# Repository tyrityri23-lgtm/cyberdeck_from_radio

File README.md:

CyberDeck from Radio
A portable cyberdeck built by converting an old radio enclosure into a functional computer with a custom keyboard, custom electronics, display, battery power and a single-board computer.
> **Submission note:** Replace the image placeholders in this README with photographs/renders of the *actual completed build* before submitting this project for review.
Overview
The goal of this project is to reuse the enclosure of an old radio and turn it into a portable computer while designing the mechanical and electronic interfaces around the new hardware.
The project is divided into four main systems:
Compute system — a single-board computer runs the operating system and applications.
Input system — a custom mechanical keyboard is scanned by a dedicated XIAO ESP32-C3 controller through an MCP23017 I/O expander.
Display and power — an internal display is mounted into the original radio opening and the computer is powered from a portable power source.
Mechanical system — custom CAD parts adapt the radio enclosure to the keyboard, electronics, display and mounting hardware.
Final Build
<!-- Replace this file with a real photo/render of the assembled final device: assets/final-model.jpg -->

The cover image for the GitHub repository should use the same real final-build photograph/render, not a concept image.
System Architecture
```mermaid
flowchart LR
    K[Mechanical keyboard switches] --> M[MCP23017 I/O expander]
    M --> E[XIAO ESP32-C3]
    E --> H[BLE HID keyboard]
    H --> C[CyberDeck computer / SBC]
    C --> D[Internal display]
    P[Power bank / battery system] --> C
    P --> E
    G[BNO055 gyroscope] --> E
    S[PMW3360 optical sensor] --> E
```
The ESP32-C3 is used as a dedicated input controller rather than making the main computer scan every switch itself. This keeps the keyboard scanning logic separate from the main operating system.
Hardware
Part	Purpose	Status / note
XIAO ESP32-C3	Keyboard controller	Used for keyboard scanning and BLE HID
MCP23017	16-bit I/O expander	Provides the GPIO used by the keyboard matrix
Mechanical switches	Keyboard input	Custom keyboard
Keycaps	Physical key interface	Custom keyboard
Single-board computer	Main computer	Choose one final platform and use it consistently in the docs
Internal display	Main visual output	Mounted in the radio enclosure
Power bank / battery system	Portable power	Verify final power wiring before publication
BNO055	Motion sensor	Mentioned by the build instructions; verify final assembly
PMW3360	Optical motion sensor	Mentioned by the build instructions; verify final assembly
Custom PCB	Keyboard/electronics board	Document the actual board revision used
Important hardware consistency check
The original repository currently mentions a Radxa X4 as the main computer in the README, while the BOM also contains a LattePanda IOTA N150 and RAM/storage parts. Before the final submission, pick the computer actually installed in the finished build and update the README, instructions, CAD and BOM so they all describe the same hardware.
Keyboard Electronics
Why use an ESP32-C3?
The main computer is responsible for running the operating system and applications. The ESP32-C3 is instead dedicated to reading the physical keyboard and handling the input-side firmware.
The MCP23017 is a 16-bit I/O expander connected over I2C. It lets the controller access more matrix lines than would be convenient using only the ESP32-C3's local GPIO.
The XIAO ESP32-C3 exposes I2C on D4/GPIO6 (SDA) and D5/GPIO7 (SCL) on the current Seeed pin map. citehttps://wiki.seeedstudio.com/XIAO_ESP32C3_Getting_Started/
```text
Keyboard switches
       |
       v
+------------------+
| Keyboard matrix  |
+------------------+
       |
       v
+------------------+       I2C       +------------------+
|   MCP23017       | <--------------> | XIAO ESP32-C3    |
| 16-bit GPIO exp. |                  | firmware         |
+------------------+                  +------------------+
                                             |
                                             v
                                      BLE HID keyboard
                                             |
                                             v
                                       Main computer
```
Matrix scanning
A keyboard matrix reduces the number of connections needed for many switches by arranging them in rows and columns. The firmware drives one row at a time and reads the column states. When a switch joins the selected row to a column, the firmware records that key as pressed.
The exact row/column mapping must match the actual PCB schematic. The firmware included in this package therefore keeps the mapping in one clearly marked configuration section instead of hiding the pin assignments throughout the code.
Schematic Documentation
Add these images from KiCad before submitting:
`assets/schematic-overview.png` — complete schematic
`assets/schematic-keyboard.png` — keyboard matrix and controller section
`assets/schematic-power.png` — power section
`assets/schematic-sensors.png` — sensor section, if the sensors are installed
For each image, add 2–4 sentences describing what the section does and why the components are connected that way.
What to explain
MCP23017 section
Explain that the MCP23017 communicates with the XIAO ESP32-C3 over I2C and exposes the GPIO used by the keyboard matrix.
Keyboard matrix section
Explain the row/column arrangement and the function of the switch diodes. The diode orientation must match the actual schematic/PCB silkscreen.
Sensor section
If the BNO055 and PMW3360 are part of the final build, document their actual buses, addresses, power voltage and interrupt/data lines from the final schematic.
Power section
Document the actual battery/power-bank output, any regulators or protection circuitry, and which subsystem receives which voltage.
PCB Design
The PCB source should be kept in the repository together with its KiCad schematic and board file.
Recommended screenshots:

PCB design goals
Keep the keyboard matrix wiring organized.
Keep I2C connections short and easy to inspect.
Provide accessible mounting holes.
Label connectors and important signals on silkscreen.
Make the board easy to assemble and troubleshoot.
Firmware
Firmware lives in `firmware/`.
Important USB detail
The ESP32-C3's integrated USB interface is USB Serial/JTAG and CDC, not a reconfigurable USB HID interface. Espressif's documentation explicitly states that the ESP32-C3 supports USB CDC and JTAG, while USB HID device support is available on ESP32-S2/S3. citeturn643326search0turn643326search2
For the current XIAO ESP32-C3 hardware, the firmware in this repository uses Bluetooth Low Energy HID for the keyboard connection. The XIAO ESP32-C3 supports Bluetooth LE, and current BLE-HID libraries support ESP32-C3. citeturn656599view0turn810315view0
If the finished PCB is required to behave as a wired USB HID keyboard, the controller should instead be changed to a USB-HID-capable ESP32-S2/S3-class device and the hardware design must be updated accordingly.
Firmware responsibilities
The firmware is responsible for:
initializing I2C;
initializing the MCP23017;
scanning the keyboard matrix;
debouncing switch transitions;
translating matrix positions into keyboard actions;
advertising/pairing as a BLE HID keyboard; and
reporting input to the host.
CAD / Mechanical Design
The CAD model should show the complete physical assembly, not just an empty shell.
Recommended assembly contents:
original radio enclosure;
display and display bracket;
keyboard plate and switches;
keyboard PCB;
XIAO ESP32-C3;
main computer/SBC;
battery/power-bank location;
mounting bosses/screws;
cable routing;
ventilation openings;
external connectors and controls;
any mouse/trackball/optical-sensor hardware actually used.
Mechanical requirements before final submission
Increase enclosure wall thickness to a clearly manufacturable value appropriate for the printing method.
Add screw bosses and mounting points where parts need to be secured.
Add openings for every connector that must be accessible from outside the case.
Add ventilation around heat-producing electronics.
Add mechanical details/design features so the enclosure looks intentionally designed rather than like a plain box.
Insert simplified electronic models into the assembly so a reviewer can understand the internal layout.
STEP Files
Export the final mechanical parts and the complete assembly to STEP and place them in `cad/step/`.
Recommended exports:
```text
cad/step/
├── final_assembly.step
├── enclosure.step
├── keyboard_plate.step
├── keyboard_case.step
└── mounting_parts.step
```
Assembly
The final assembly should be documented with photos showing the progression from subassemblies to the complete device.
```text
PCB assembly
    ↓
Keyboard assembly
    ↓
Electronics mounted in case
    ↓
Display installed
    ↓
Power and signal wiring
    ↓
Final enclosure closed
    ↓
Boot/test
```
Testing
Record the results of these tests before final submission:
Test	Result	Evidence
ESP32-C3 powers on	TODO	Photo/video
MCP23017 detected on I2C	TODO	Serial log
Every keyboard key works	TODO	Key test
BLE keyboard pairs	TODO	Host screenshot
Display works	TODO	Photo
Main computer boots	TODO	Photo
Power system works safely	TODO	Test notes
Final enclosure fits	TODO	Final photo
Sensors work (if installed)	TODO	Serial/test result
Bill of Materials
The existing `bom.csv` contains the component list and purchase links. Clean it up before submission so that it only contains the actual parts used by the final build, with correct quantities and prices.
In particular, reconcile the current computer choice and verify that the sensor and PCB parts listed in the build instructions also appear in the BOM when they are actually used.
Repository Structure
```text
cyberdeck_from_radio/
├── README.md
├── instructions.md
├── bom.csv
├── firmware/
│   ├── platformio.ini
│   ├── README.md
│   └── src/
│       └── main.cpp
├── docs/
│   ├── SCHEMATIC_GUIDE.md
│   ├── CAD_AND_RENDER_GUIDE.md
│   └── FINAL_SUBMISSION_CHECKLIST.md
├── assets/
│   ├── final-model.jpg
│   ├── schematic-overview.png
│   ├── schematic-keyboard.png
│   ├── pcb-front.png
│   ├── pcb-back.png
│   └── pcb-3d.png
├── cad/
│   └── step/
└── Footprints_and__libraries/
```
Current Limitations / Next Steps
The final version should only mark a feature as complete after it has been physically tested. Hardware that is planned but not installed should remain clearly labelled as planned.
Credits
Built as an independent hardware project using KiCad for electronics design, CAD software for the mechanical design, and embedded firmware for the custom input controller.
References
Seeed Studio XIAO ESP32-C3 documentation — board pin map and BLE capability. citeturn656599view0
Espressif ESP32-C3 documentation — USB Serial/JTAG and CDC limitations. citeturn643326search0turn643326search2
Adafruit MCP23017 Arduino documentation — I2C GPIO-expander usage. citeturn643326search7

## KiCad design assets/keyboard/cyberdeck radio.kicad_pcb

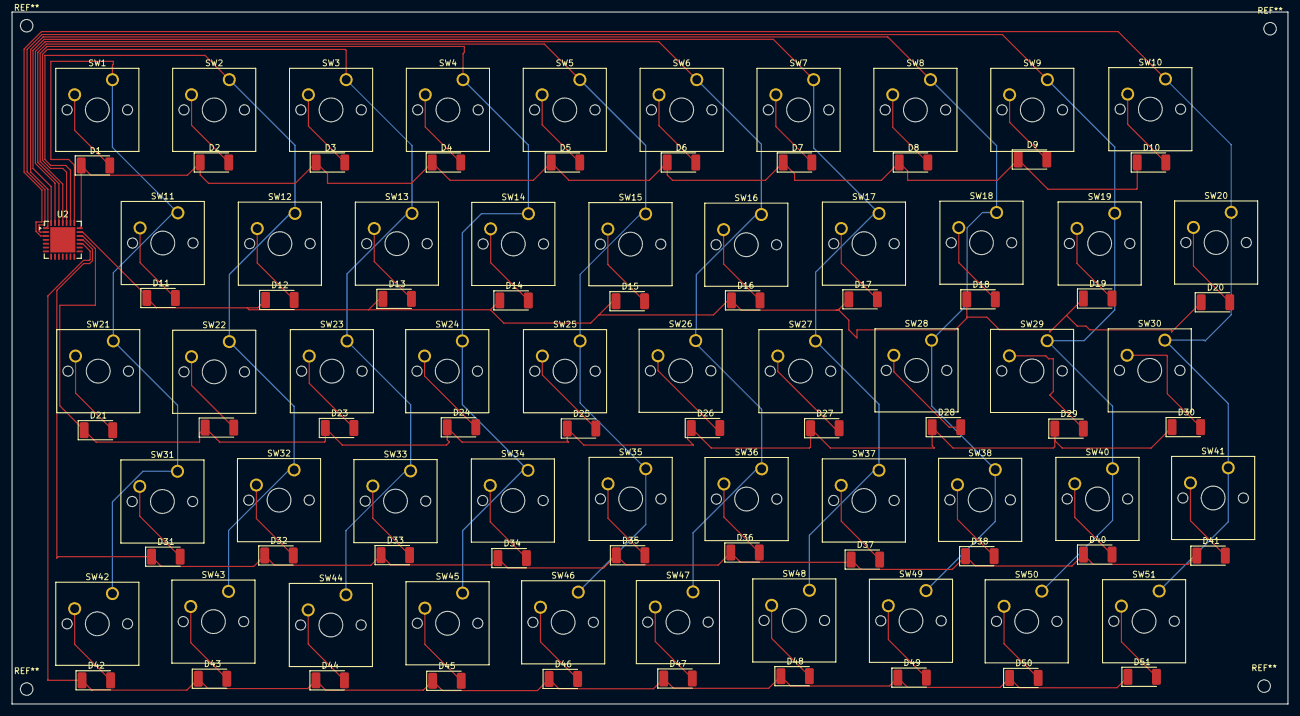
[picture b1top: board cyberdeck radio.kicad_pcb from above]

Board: 2 copper layers, 214.5 x 116.3 mm, 101 parts (0 on the bottom side), 66 nets.

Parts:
D1, D2, D3, D4, D5, D6, D7, D8, D9, D10, D11, D12, D13, D14, D15, D16, D17, D18, D19, D20, D21, D22, D23, D24, D25, D26, D27, D28, D29, D30, D31, D32, D33, D34, D35, D36, D37, D38, D40, D41, D42, D43, D44, D45, D46, D47, D48, D49, D50, D51: SM5059; D_MELF
SW1, SW2, SW3, SW4, SW5, SW6, SW7, SW8, SW9, SW10, SW11, SW12, SW13, SW14, SW15, SW16, SW17, SW18, SW19, SW20, SW21, SW22, SW23, SW24, SW25, SW26, SW27, SW28, SW29, SW30, SW31, SW32, SW33, SW34, SW35, SW36, SW37, SW38, SW40, SW41, SW42, SW43, SW44, SW45, SW46, SW47, SW48, SW49, SW50, SW51: SW_Push_45deg; SW_Cherry_MX_1.00u_PCB
U2: MCP23017x-x-ML; QFN-28-1EP_6x6mm_P0.65mm_EP4.25x4.25mm

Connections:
+3.3V: U2.5 (V_{DD}), U2.11 (A0), U2.12 (A1), U2.13 (A2), U2.14 (~RESET)
unnamed: D1.2 (A), SW1.2
unnamed: D2.2 (A), SW2.2
unnamed: D3.2 (A), SW3.2
unnamed: D4.2 (A), SW4.2
unnamed: D5.2 (A), SW5.2
unnamed: D6.2 (A), SW6.2
unnamed: D7.2 (A), SW7.2
unnamed: D8.2 (A), SW8.2
unnamed: D9.2 (A), SW9.2
unnamed: D10.2 (A), SW10.2
unnamed: D11.2 (A), SW11.2
unnamed: D12.2 (A), SW12.2
unnamed: D13.2 (A), SW13.2
unnamed: D14.2 (A), SW14.2
unnamed: D15.2 (A), SW15.2
unnamed: D16.2 (A), SW16.2
unnamed: D17.2 (A), SW17.2
unnamed: D18.2 (A), SW18.2
unnamed: D19.2 (A), SW19.2
unnamed: D20.2 (A), SW20.2
unnamed: D21.2 (A), SW21.2
unnamed: D22.2 (A), SW22.2
unnamed: D23.2 (A), SW23.2
unnamed: D24.2 (A), SW24.2
unnamed: D25.2 (A), SW25.2
unnamed: D26.2 (A), SW26.2
unnamed: D27.2 (A), SW27.2
unnamed: D28.2 (A), SW28.2
unnamed: D29.2 (A), SW29.2
unnamed: D30.2 (A), SW30.2
unnamed: D31.2 (A), SW31.2
unnamed: D32.2 (A), SW32.2
unnamed: D33.2 (A), SW33.2
unnamed: D34.2 (A), SW34.2
unnamed: D35.2 (A), SW35.2
unnamed: D36.2 (A), SW36.2
unnamed: D37.2 (A), SW37.2
unnamed: D38.2 (A), SW38.2
unnamed: D40.2 (A), SW40.2
unnamed: D41.2 (A), SW41.2
unnamed: D42.2 (A), SW42.2
unnamed: D43.2 (A), SW43.2
unnamed: D44.2 (A), SW44.2
unnamed: D45.2 (A), SW45.2
unnamed: D46.2 (A), SW46.2
unnamed: D47.2 (A), SW47.2
unnamed: D48.2 (A), SW48.2
unnamed: D49.2 (A), SW49.2
unnamed: D50.2 (A), SW50.2
unnamed: D51.2 (A), SW51.2
colum1: SW1.1, SW11.1, SW21.1, SW31.1, SW42.1, U2.22 (GPA5)
colum2: SW2.1, SW12.1, SW22.1, SW32.1, SW43.1, U2.23 (GPA6)
colum3: SW3.1, SW13.1, SW23.1, SW33.1, SW44.1, U2.24 (GPA7)
colum4: SW4.1, SW14.1, SW24.1, SW34.1, SW45.1, U2.25 (GPB0)
colum5: SW5.1, SW15.1, SW25.1, SW35.1, SW46.1, U2.26 (GPB1)
colum6: SW6.1, SW16.1, SW26.1, SW36.1, SW47.1, U2.27 (GPB2)
colum7: SW7.1, SW17.1, SW27.1, SW37.1, SW48.1, U2.28 (GPB3)
colum8: SW8.1, SW18.1, SW28.1, SW38.1, SW49.1, U2.1 (GPB4)
colum9: SW9.1, SW19.1, SW29.1, SW40.1, SW50.1, U2.2 (GPB5)
colum10: SW10.1, SW20.1, SW30.1, SW41.1, SW51.1, U2.3 (GPB6)
row1: D1.1 (K), D2.1 (K), D3.1 (K), D4.1 (K), D5.1 (K), D6.1 (K), D7.1 (K), D8.1 (K), D9.1 (K), D10.1 (K), U2.21 (GPA4)
row2: D11.1 (K), D12.1 (K), D13.1 (K), D14.1 (K), D15.1 (K), D16.1 (K), D17.1 (K), D18.1 (K), D19.1 (K), D20.1 (K), U2.20 (GPA3)
row3: D21.1 (K), D22.1 (K), D23.1 (K), D24.1 (K), D25.1 (K), D26.1 (K), D27.1 (K), D28.1 (K), D29.1 (K), D30.1 (K), U2.19 (GPA2)
row4: D31.1 (K), D32.1 (K), D33.1 (K), D34.1 (K), D35.1 (K), D36.1 (K), D37.1 (K), D38.1 (K), D40.1 (K), D41.1 (K), U2.18 (GPA1)
row5: D42.1 (K), D43.1 (K), D44.1 (K), D45.1 (K), D46.1 (K), D47.1 (K), D48.1 (K), D49.1 (K), D50.1 (K), D51.1 (K), U2.17 (GPA0)

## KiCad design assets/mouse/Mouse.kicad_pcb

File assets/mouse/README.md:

## DIY Mouse:
so this is the mouse for the cyberdeck radio i did a different readme so its more clean and tighty. So this uses a laser for all the movement and an esp32 so again i dont put alot of load on the sbc cause it will be running the os. Moreover it uses 4 buttons 2 for the left and right and 2 side buttons with custom micros. Also a rotary encoder for scroling and i made it as small as possible at 4cm*4cm

## Hardware:

* Seeed Studio XIAO ESP32-C3 

* PixArt PMW3360DM-T2QU sensor

* My mouse pcb

* AP2112K voltage regulator

* MCP23017 I/O 

## PCB & Sensor Routing:
So to make this fully custom i designed the pcb myself it took me a while but not as long as the keyboard cause i alredy knew the basics. The best part is that i could make it any shape i wanted so i put the rotary encoder on the side cause it looks really cool 

## Current Status:

i finished everything even the case and the code all that is left now is to get everything shipped and assembled 

## BMO:

| Item | Quantity | Source / Designer Link | Price (€/$) |
| --- | --- | --- | --- |
| PMW3360DM-T2QU | 1 | [AliExpress Link](https://tr.aliexpress.com/item/1005005318848362.html?gatewayAdapt=glo2tur) | 13 |
| tactile button click switch | 50pcs | [AliExpress Link](https://tr.aliexpress.com/item/1005003792387482.html) | 13 |
| AP2112K | 10pcs | [AliExpress Link](https://tr.aliexpress.com/item/32998839398.html) | 13 |
| resistors | 1 box | [AliExpress Link](https://tr.aliexpress.com/item/1005011772534173.html) | 15 |
| mcp23017 | 1 | [AliExpress Link](https://tr.aliexpress.com/item/1005012543943820.html) | 2 |
| rotery encoder | 5pcs | [AliExpress Link](https://tr.aliexpress.com/item/1005005181295203.html) | 2 |
| esp32 | 3 | [Seeed Studio Link](https://www.seeedstudio.com/Seeed-Studio-XIAO-ESP32C3-3PCS-p-5920.html) | 13 |
| pcb | 8 | [JLCPCB Link](https://cart.jlcpcb.com/quote?businessType=projectFile&fileAccessId=8775813919665467392&bomId&cplId&projectBizKey=610380259701374978) | 23 |

I will continue updating the repository as the custom wireless mouse hardware comes together. Once all the parts arrive and the build begins I will add assembly photos, firmware and documentation covering the process of the mouse build.

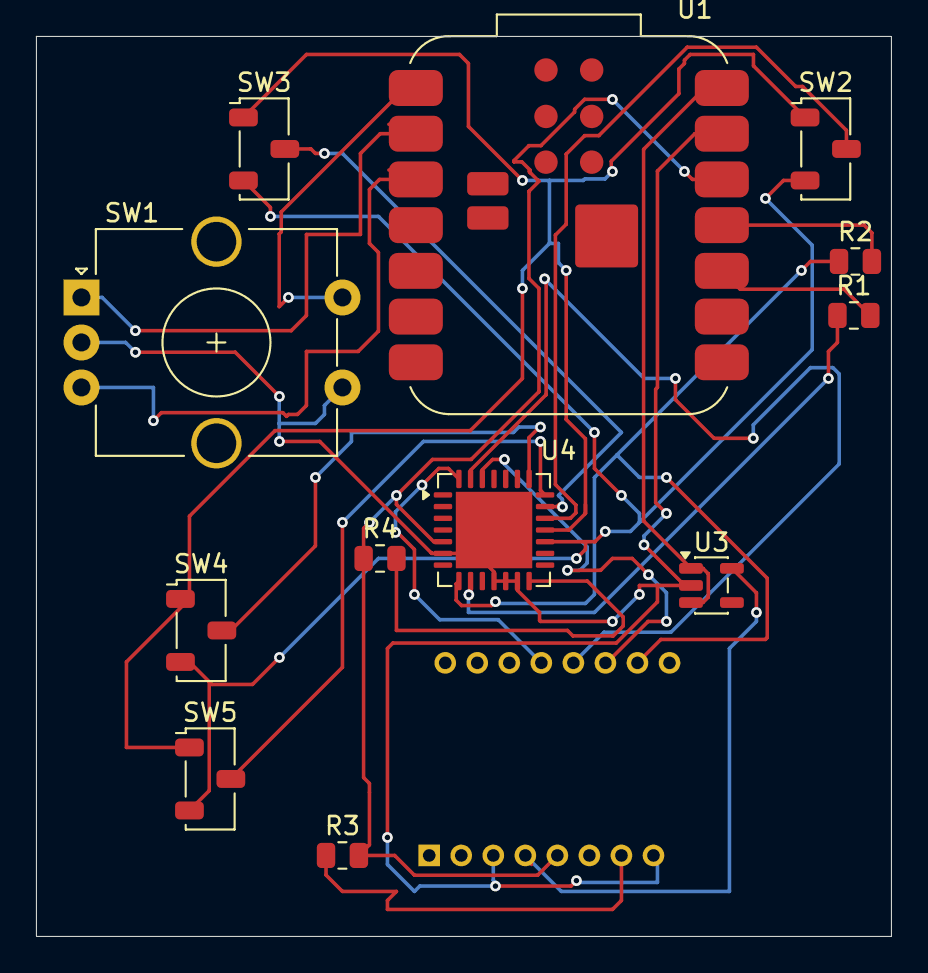
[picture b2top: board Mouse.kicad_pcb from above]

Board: 2 copper layers, 47.5 x 50.0 mm, 13 parts (0 on the bottom side), 22 nets.

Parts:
R1, R2, R3, R4: R; R_0805_2012Metric
SW1: RotaryEncoder_Switch; RotaryEncoder_Alps_EC12E-Switch_Vertical_H20mm_CircularMoun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
SW2, SW3, SW4, SW5: SW_Nidec_CAS-120A1; Nidec_Copal_CAS-120A
U1: XIAO ESP32C3; MCU_Seeed_ESP32C3
U2: PMW3360DM-T2QU; DIP-16_W10.16mm
U3: AP2112K-1.8; SOT-23-5
U4: MCP23017x-x-ML; QFN-28-1EP_6x6mm_P0.65mm_EP4.25x4.25mm

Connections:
1: SW2.3 (A), SW3.3 (A), SW4.3 (A), SW5.3 (A), U4.17 (GPA0)
2: SW2.1 (C), SW3.1 (C), SW4.1 (C), SW5.1 (C), U4.18 (GPA1)
3: SW2.2 (B), U4.19 (GPA2)
4: SW3.2 (B), U4.20 (GPA3)
5: SW5.2 (B), U4.21 (GPA4)
6: SW4.2 (B), U4.22 (GPA5)
10: U2.11 (MOSI), U4.26 (GPB1)
11: U2.12 (MISO), U4.27 (GPB2)
12: U2.13 (NCS), U4.28 (GPB3)
+1V8: U2.4 (VDD), U3.5 (VOUT)
GND: SW1.C, SW1.S2, U1.13 (GND), U2.3 (VDDPIX), U2.8 (GND), U3.2 (GND), U4.6 (V_{SS}), U4.11 (A0), U4.12 (A1), U4.13 (A2), U4.29 (EP)
unnamed: SW1.S1, U1.1 (D0)
unnamed: SW1.A, U1.2 (D1)
unnamed: SW1.B, U1.3 (D2)
unnamed: R1.2, U1.10 (D9)
unnamed: R2.2, U1.11 (D10)
unnamed: R3.2, R4.1, U1.12 (VCC_3V3), U2.5 (VDDIO), U4.5 (V_{DD})
unnamed: U1.14 (VUSB), U3.1 (VIN), U3.3 (EN)
unnamed: R2.1, U2.10 (SCLK), U4.8 (SCK)
unnamed: R3.1, U2.7 (~RESET)
unnamed: R1.1, U4.9 (SDA)
unnamed: R4.2, U4.14 (~RESET)
